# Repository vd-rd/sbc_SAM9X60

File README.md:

# Microchip SAM9X60 SBC

This board embeds a SIP (single core 600MHz ARM926 with 1Gb DDR2) with ACT8945a PMIC, IO headers and microSD/eMMC storage.

Board overview (draft):
[TBD]

## Board features
| Characteristic | Description |
| --- | --- |
| Dimensions | 60mm x 40mm |
| Processor | Microchip SAM9X60 @600MHz |
| Oscillators | 32.768kHz slow clock, 24MHz main clock |
| RAM | 128MB embedded DDR2 memory |
| Storage | microSD/eMMC |
| USB | 1 microUSB client |
| Ethernet | 2 10/100M RMII with pins on header |
| WiFi | 1 SDIO adapter with wifi/bt combo |
| Supply | Power path between USB/Vin/Battery, 5V max |

## Notes and observations
[TBD]

## Resources

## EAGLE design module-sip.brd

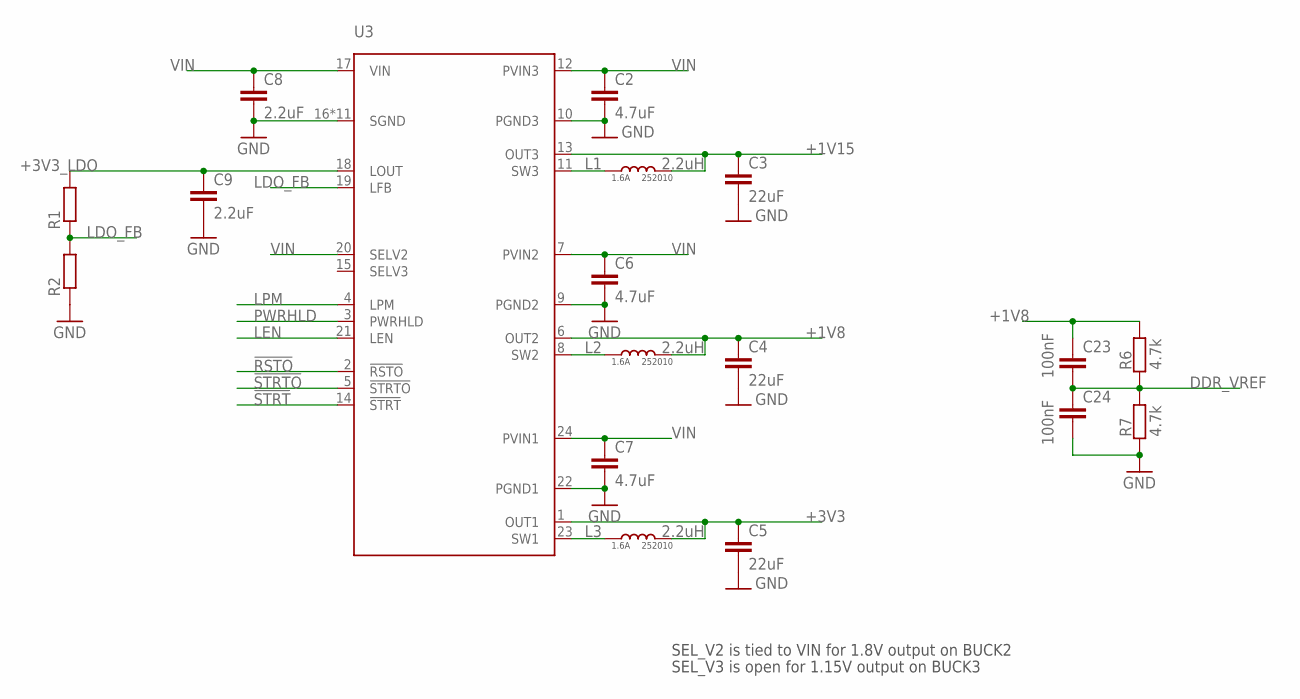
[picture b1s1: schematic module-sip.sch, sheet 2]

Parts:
C2, C6, C7: 4.7uF; C0603
C3, C4, C5: 22uF; C0805
C8, C9: 2.2uF; C0603
C23, C24: 100nF; C0402
L1, L2, L3: 2.2uH; INDUCTOR2520
R1, R2: R-EU_R0402; R0402
R6, R7: 4.7k; R0402
U3: MCP16501; QFN50P400X400X90-25T270N

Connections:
!RSTO: U3.2 (!RSTO)
!STRT: U3.14 (!STRT)
!STRTO: U3.5 (!STRTO)
+1V8: C4.1, C23.1, L2.P$2 (2), R6.2, U3.6 (OUT2); also elsewhere on the board
+1V15: C3.1, L1.P$2 (2), U3.13 (OUT3); also elsewhere on the board
+3V3: C5.1, L3.P$2 (2), U3.1 (OUT1); also elsewhere on the board
+3V3_LDO: C9.1, R1.2, U3.18 (LOUT)
DDR_VREF: C23.2, C24.1, R6.1, R7.2; also elsewhere on the board
GND: C2.2, C3.2, C4.2, C5.2, C6.2, C7.2, C8.2, C9.2, C24.2, R2.1, R7.1, U3.9 (PGND2), U3.10 (PGND3), U3.16 (SGND), U3.22 (PGND1), U3.25 (SGND), U3.P$1 (SGND), U3.P$2 (SGND), U3.P$3 (SGND), U3.P$4 (SGND), U3.P$5 (SGND), U3.P$6 (SGND), U3.P$7 (SGND), U3.P$8 (SGND), U3.P$9 (SGND); also elsewhere on the board
LDO_FB: R1.1, R2.2, U3.19 (LFB)
LEN: U3.21 (LEN)
LPM: U3.4 (LPM)
unnamed: L1.P$1 (1), U3.11 (SW3)
unnamed: L2.P$1 (1), U3.8 (SW2)
unnamed: L3.P$1 (1), U3.23 (SW1)
PWRHLD: U3.3 (PWRHLD)
VIN: C2.1, C6.1, C7.1, C8.1, U3.7 (PVIN2), U3.12 (PVIN3), U3.17 (VIN), U3.20 (SELV2), U3.24 (PVIN1)

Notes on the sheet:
SEL_V2 is tied to VIN for 1.8V output on BUCK2
SEL_V3 is open for 1.15V output on BUCK3

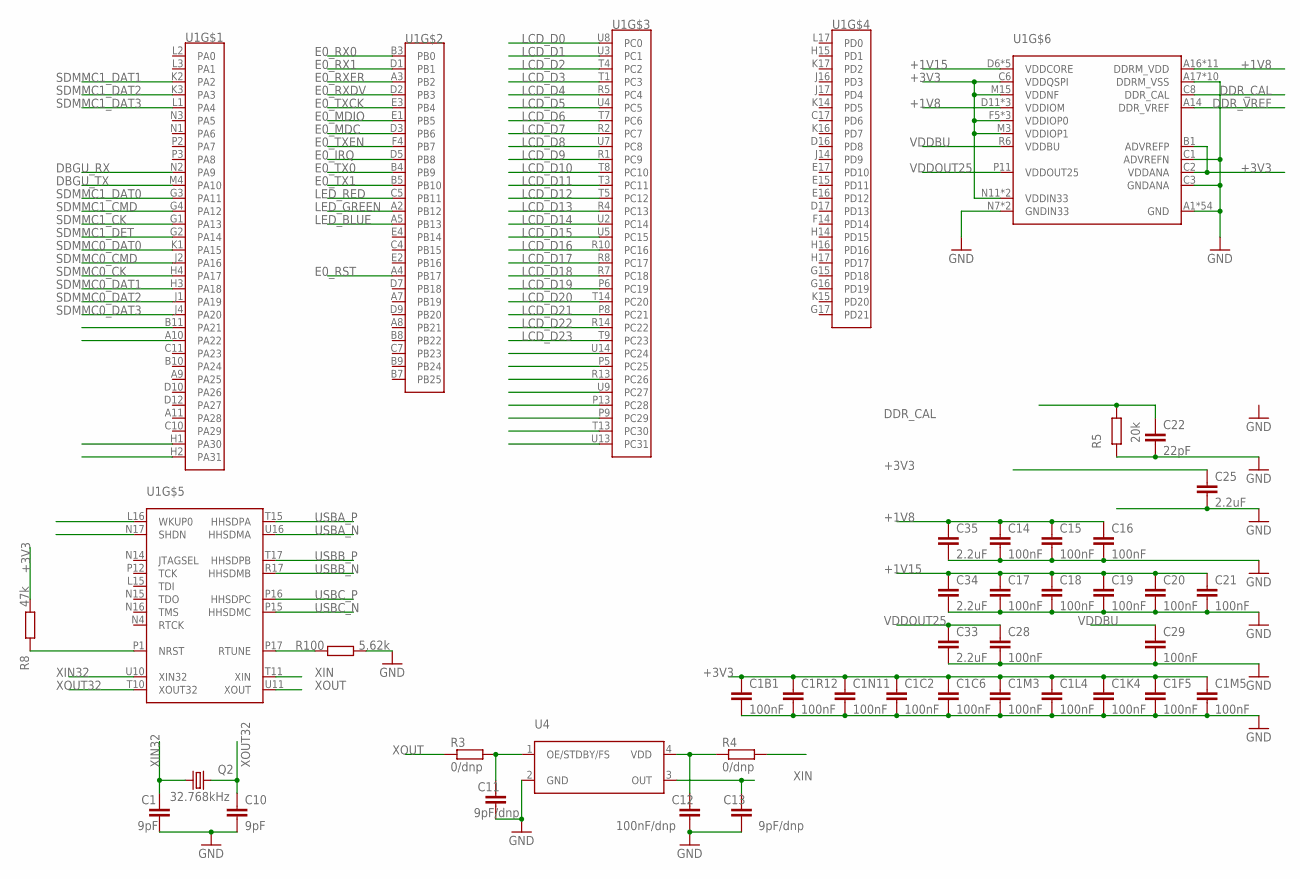
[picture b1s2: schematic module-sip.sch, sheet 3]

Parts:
C1, C10: 9pF; C0402
C1B1, C1C2, C1C6, C1F5, C1K4, C1L4, C1M3, C1M5, C1N11, C1R12, C14, C15, C16, C17, C18, C19, C20, C21, C28, C29: 100nF; C0201
C11, C13: 9pF/dnp; C0402
C12: 100nF/dnp; C0402
C22: 22pF; C0402
C25, C33, C34, C35: 2.2uF; C0402
Q2: 32.768kHz; 3215
R3, R4: 0/dnp; R0402
R5: 20k; R0402
R8: 47k; R0402
R100: 5.62k; R0402
U1: SAM9X60-D1G; BGA289C80P17X17_1400X1400X120N
U4: DSC1001CXX-024.0000; DFN320X250X90-4N

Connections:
+1V8: C14.1, C15.1, C16.1, C35.1, U1.A16 (DDRM_VDD), U1.B15 (DDRM_VDD), U1.B17 (DDRM_VDD), U1.C14 (DDRM_VDD), U1.C16 (DDRM_VDD), U1.D11 (VDDIOM), U1.D13 (DDRM_VDD), U1.D15 (DDRM_VDD), U1.E11 (DDRM_VDD), U1.E12 (DDRM_VDD), U1.E14 (VDDIOM), U1.F13 (DDRM_VDD), U1.G13 (DDRM_VDD), U1.G14 (VDDIOM); also elsewhere on the board
+1V15: C17.1, C18.1, C19.1, C20.1, C21.1, C34.1, U1.D6 (VDDCORE), U1.D8 (VDDCORE), U1.G5 (VDDCORE), U1.L6 (VDDCORE), U1.M7 (VDDCORE); also elsewhere on the board
+3V3: C1B1.1, C1C2.1, C1C6.1, C1F5.1, C1K4.1, C1L4.1, C1M3.1, C1M5.1, C1N11.1, C1R12.1, C25.1, R8.2, U1.B1 (ADVREFP), U1.C2 (VDDANA), U1.C6 (VDDQSPI), U1.F5 (VDDIOP0), U1.K4 (VDDIOP0), U1.L4 (VDDIOP0), U1.M3 (VDDIOP1), U1.M15 (VDDNF), U1.N11 (VDDIN33), U1.R12 (VDDIN33); also elsewhere on the board
DBGU_RX: U1.N2 (PA9); also elsewhere on the board
DBGU_TX: U1.M4 (PA10); also elsewhere on the board
DDR_CAL: C22.1, R5.1, U1.C8 (DDR_CAL)
DDR_VREF: U1.A14 (DDR_VREF); also elsewhere on the board
E0_IRQ: U1.D5 (PB8); also elsewhere on the board
E0_MDC: U1.D3 (PB6); also elsewhere on the board
E0_MDIO: U1.E1 (PB5); also elsewhere on the board
E0_RST: U1.A4 (PB17)
E0_RX0: U1.B3 (PB0); also elsewhere on the board
E0_RX1: U1.D1 (PB1); also elsewhere on the board
E0_RXDV: U1.D2 (PB3); also elsewhere on the board
E0_RXER: U1.A3 (PB2); also elsewhere on the board
E0_TX0: U1.B4 (PB9); also elsewhere on the board
E0_TX1: U1.B5 (PB10); also elsewhere on the board
E0_TXCK: U1.E3 (PB4); also elsewhere on the board
E0_TXEN: U1.F4 (PB7); also elsewhere on the board
GND: C1.2, C1B1.2, C1C2.2, C1C6.2, C1F5.2, C1K4.2, C1L4.2, C1M3.2, C1M5.2, C1N11.2, C1R12.2, C10.2, C11.2, C12.2, C13.2, C14.2, C15.2, C16.2, C17.2, C18.2, C19.2, C20.2, C21.2, C22.2, C25.2, C28.2, C29.2, C33.2, C34.2, C35.2, R5.2, R100.2, U1.A1 (GND), U1.A13 (GND), U1.A15 (GND), U1.A17 (DDRM_VSS), U1.B2 (GND), U1.B13 (GND), U1.B14 (GND), U1.B16 (DDRM_VSS), U1.C1 (ADVREFN), U1.C3 (GNDANA), U1.C9 (GND), U1.C12 (DDRM_VSS), U1.C13 (GND), U1.C15 (DDRM_VSS), U1.D4 (GND), U1.D14 (DDRM_VSS), U1.E5 (GND), U1.E6 (GND), U1.E7 (GND), U1.E13 (DDRM_VSS), U1.F3 (GND), U1.F6 (GND), U1.F7 (GND), U1.F11 (DDRM_VSS), U1.F12 (DDRM_VSS), U1.F15 (DDRM_VSS), U1.G6 (GND), U1.G12 (DDRM_VSS), U1.H8 (GND), U1.H9 (GND), U1.H10 (GND), U1.J3 (GND), U1.J8 (GND), U1.J9 (GND), U1.J10 (GND), U1.J15 (GND), U1.K8 (GND), U1.K9 (GND), U1.K10 (GND), U1.L5 (GND), U1.L12 (GND), U1.L13 (GND), U1.L14 (GND), U1.M5 (GND), U1.M6 (GND), U1.M11 (GND), U1.M12 (GND), U1.M13 (GND), U1.M14 (GND), U1.N5 (GND), U1.N6 (GND), U1.N7 (GNDIN33), U1.N12 (GND), U1.N13 (GND), U1.P4 (GND), U1.P7 (GNDIN33), U1.P10 (GND), U1.P14 (GND), U1.R3 (GND), U1.R9 (GND), U1.R11 (GND), U1.R15 (GND), U1.R16 (GND), U1.T2 (GND), U1.T16 (GND), U1.U1 (GND), U1.U15 (GND), U1.U17 (GND), U4.2 (GND); also elsewhere on the board
LCD_D0: U1.U8 (PC0)
LCD_D1: U1.U3 (PC1)
LCD_D2: U1.T4 (PC2)
LCD_D3: U1.T1 (PC3)
LCD_D4: U1.R5 (PC4)
LCD_D5: U1.U4 (PC5)
LCD_D6: U1.T7 (PC6)
LCD_D7: U1.R2 (PC7)
LCD_D8: U1.U7 (PC8)
LCD_D9: U1.R1 (PC9)
LCD_D10: U1.T8 (PC10)
LCD_D11: U1.T3 (PC11)
LCD_D12: U1.T5 (PC12)
LCD_D13: U1.R4 (PC13)
LCD_D14: U1.U2 (PC14)
LCD_D15: U1.U5 (PC15)
LCD_D16: U1.R10 (PC16)
LCD_D17: U1.R8 (PC17)
LCD_D18: U1.R7 (PC18)
LCD_D19: U1.P6 (PC19)
LCD_D20: U1.T14 (PC20)
LCD_D21: U1.P8 (PC21)
LCD_D22: U1.R14 (PC22)
LCD_D23: U1.T9 (PC23)
LED_BLUE: U1.A5 (PB13); also elsewhere on the board
LED_GREEN: U1.A2 (PB12); also elsewhere on the board
LED_RED: U1.C5 (PB11); also elsewhere on the board
unnamed: C12.1, R4.1, U4.4 (VDD)
unnamed: C11.1, R3.2, U4.1 (OE/STDBY/FS)
unnamed: R8.1, U1.P1 (NRST)
unnamed: R100.1, U1.P17 (RTUNE)
SDMMC0_CK: U1.H4 (PA17)
SDMMC0_CMD: U1.J2 (PA16); also elsewhere on the board
SDMMC0_DAT0: U1.K1 (PA15); also elsewhere on the board
SDMMC0_DAT1: U1.H3 (PA18); also elsewhere on the board
SDMMC0_DAT2: U1.J1 (PA19); also elsewhere on the board
SDMMC0_DAT3: U1.J4 (PA20); also elsewhere on the board
SDMMC1_CK: U1.G1 (PA13); also elsewhere on the board
SDMMC1_CMD: U1.G4 (PA12); also elsewhere on the board
SDMMC1_DAT0: U1.G3 (PA11); also elsewhere on the board
SDMMC1_DAT1: U1.K2 (PA2); also elsewhere on the board
SDMMC1_DAT2: U1.K3 (PA3); also elsewhere on the board
SDMMC1_DAT3: U1.L1 (PA4); also elsewhere on the board
SDMMC1_DET: U1.G2 (PA14); also elsewhere on the board
USBA_N: U1.U16 (HHSDMA); also elsewhere on the board
USBA_P: U1.T15 (HHSDPA); also elsewhere on the board
USBB_N: U1.R17 (HHSDMB); also elsewhere on the board
USBB_P: U1.T17 (HHSDPB); also elsewhere on the board
USBC_N: U1.P15 (HHSDMC); also elsewhere on the board
USBC_P: U1.P16 (HHSDPC); also elsewhere on the board
VDDBU: C29.1, U1.R6 (VDDBU)
VDDOUT25: C28.1, C33.1, U1.P11 (VDDOUT25)
XIN: C13.1, U1.T11 (XIN), U4.3 (OUT)
XIN32: C1.1, Q2.1, U1.U10 (XIN32)
XOUT: R3.1, U1.U11 (XOUT)
XOUT32: C10.1, Q2.2, U1.T10 (XOUT32)

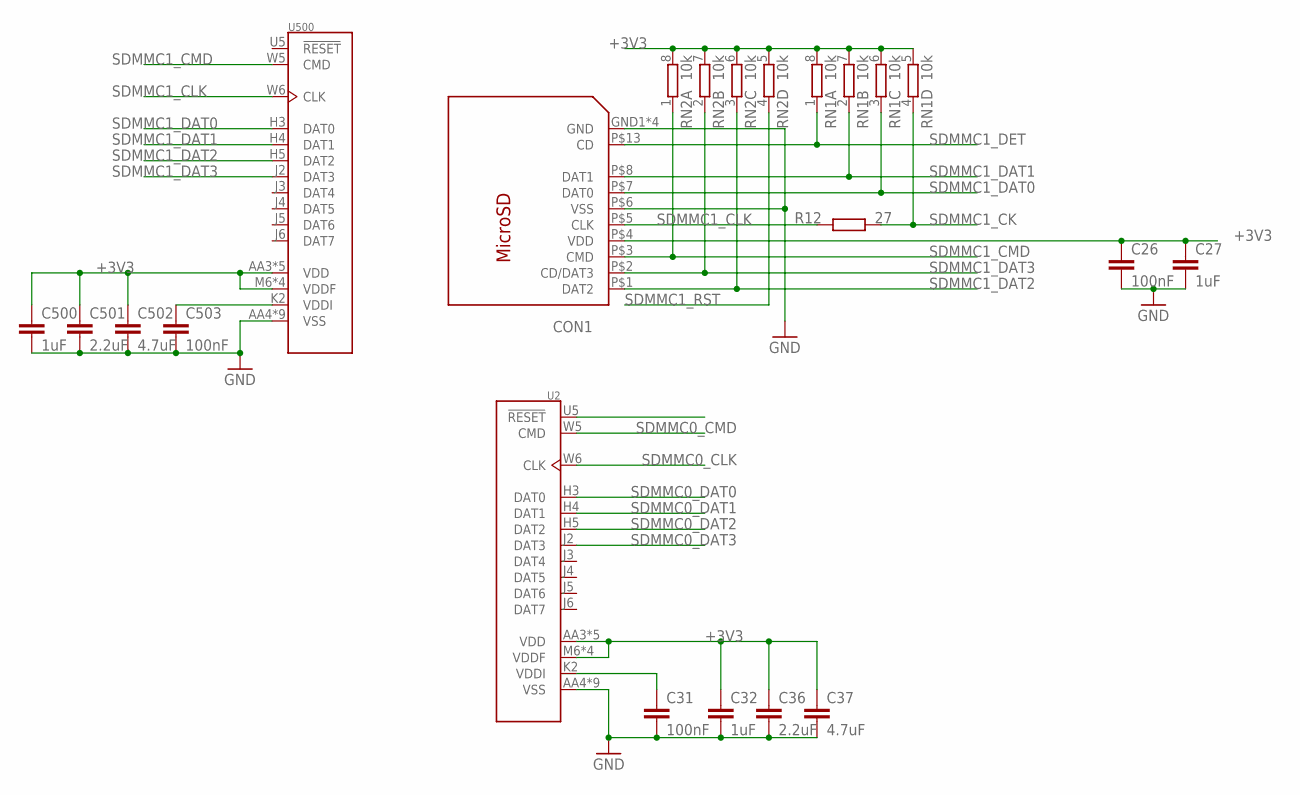
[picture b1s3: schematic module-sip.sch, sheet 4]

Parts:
C26, C31, C503: 100nF; C0402
C27, C32, C500: 1uF; C0402
C36, C501: 2.2uF; C0402
C37, C502: 4.7uF; C0402
CON1: 112J-TXAR; 112J
R12: 27; R0402
RN1, RN2: 10k; 4X0402ARV341
U2, U500: KLMXGXGE4A-A001; BGA169C50P14X28_1600X1200X120N

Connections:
+3V3: C26.1, C27.1, C32.1, C36.1, C37.1, C500.1, C501.1, C502.1, CON1.P$4 (VDD), RN1.5 (2), RN1.6 (2), RN1.7 (2), RN1.8 (2), RN2.5 (2), RN2.6 (2), RN2.7 (2), RN2.8 (2), U2.AA3 (VDD), U2.AA5 (VDD), U2.K6 (VDD), U2.M6 (VDDF), U2.N5 (VDDF), U2.T10 (VDDF), U2.U9 (VDDF), U2.W4 (VDD), U2.Y4 (VDD), U500.AA3 (VDD), U500.AA5 (VDD), U500.K6 (VDD), U500.M6 (VDDF), U500.N5 (VDDF), U500.T10 (VDDF), U500.U9 (VDDF), U500.W4 (VDD), U500.Y4 (VDD); also elsewhere on the board
GND: C26.2, C27.2, C31.2, C32.2, C36.2, C37.2, C500.2, C501.2, C502.2, C503.2, CON1.GND1 (GND), CON1.GND2 (GND), CON1.GND3 (GND), CON1.GND4 (GND), CON1.P$6 (VSS), U2.AA4 (VSS), U2.AA6 (VSS), U2.K4 (VSS), U2.M7 (VSS), U2.P5 (VSS), U2.R10 (VSS), U2.U8 (VSS), U2.Y2 (VSS), U2.Y5 (VSS), U500.AA4 (VSS), U500.AA6 (VSS), U500.K4 (VSS), U500.M7 (VSS), U500.P5 (VSS), U500.R10 (VSS), U500.U8 (VSS), U500.Y2 (VSS), U500.Y5 (VSS); also elsewhere on the board
unnamed: C503.1, U500.K2 (VDDI)
unnamed: C31.1, U2.K2 (VDDI)
SDMMC0_CLK: U2.W6 (CLK)
SDMMC0_CMD: U2.W5 (CMD); also elsewhere on the board
SDMMC0_DAT0: U2.H3 (DAT0); also elsewhere on the board
SDMMC0_DAT1: U2.H4 (DAT1); also elsewhere on the board
SDMMC0_DAT2: U2.H5 (DAT2); also elsewhere on the board
SDMMC0_DAT3: U2.J2 (DAT3); also elsewhere on the board
SDMMC1_CK: R12.2, RN1.4 (1); also elsewhere on the board
SDMMC1_CLK: CON1.P$5 (CLK), R12.1, U500.W6 (CLK)
SDMMC1_CMD: CON1.P$3 (CMD), RN2.1, U500.W5 (CMD); also elsewhere on the board
SDMMC1_DAT0: CON1.P$7 (DAT0), RN1.3 (1), U500.H3 (DAT0); also elsewhere on the board
SDMMC1_DAT1: CON1.P$8 (DAT1), RN1.2 (1), U500.H4 (DAT1); also elsewhere on the board
SDMMC1_DAT2: CON1.P$1 (DAT2), RN2.3 (1), U500.H5 (DAT2); also elsewhere on the board
SDMMC1_DAT3: CON1.P$2 (CD/DAT3), RN2.2 (1), U500.J2 (DAT3); also elsewhere on the board
SDMMC1_DET: CON1.P$13 (CD), RN1.1; also elsewhere on the board
SDMMC1_RST: RN2.4 (1)

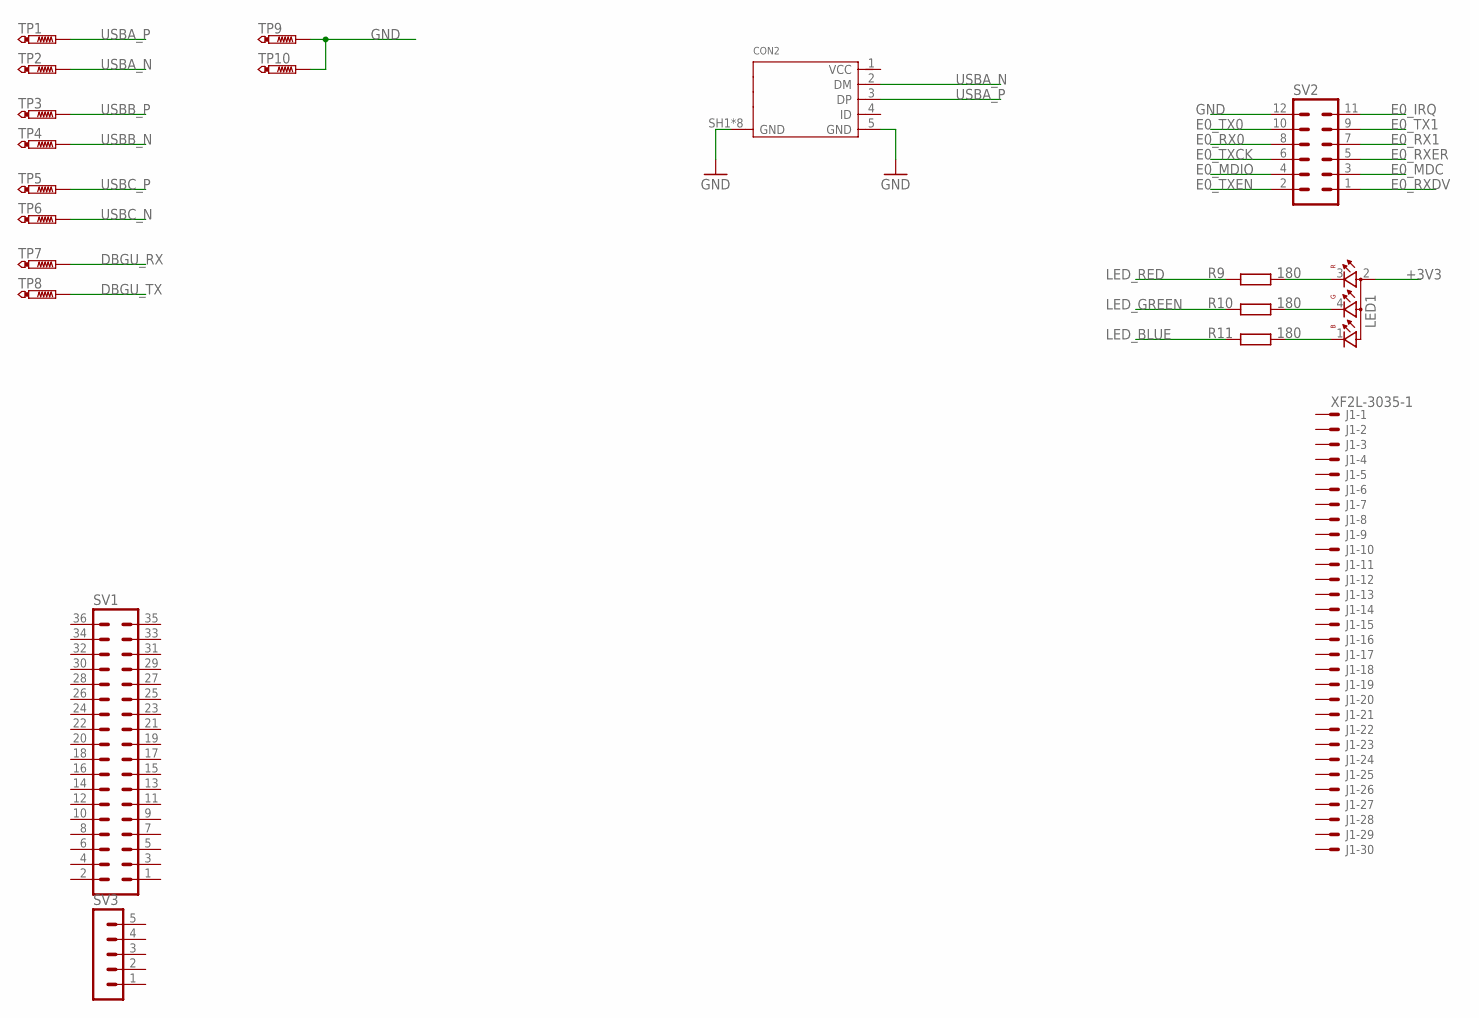
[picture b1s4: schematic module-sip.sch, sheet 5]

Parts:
CON2: 10118194-0001LF; 10118194
J1: XF2L-3035-1
LED1: OSTB1204C1E; 321015RGB
R9, R10, R11: 180; R0402
SV1: MA18-2
SV2: MA06-2
SV3: MA05-1
TP1, TP2, TP3, TP4, TP5, TP6, TP7, TP8, TP9, TP10: PTR1B1,27; B1,27

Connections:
+3V3: LED1.2 (CC); also elsewhere on the board
DBGU_RX: TP7.TP; also elsewhere on the board
DBGU_TX: TP8.TP; also elsewhere on the board
E0_IRQ: SV2.11; also elsewhere on the board
E0_MDC: SV2.3; also elsewhere on the board
E0_MDIO: SV2.4; also elsewhere on the board
E0_RX0: SV2.8; also elsewhere on the board
E0_RX1: SV2.7; also elsewhere on the board
E0_RXDV: SV2.1; also elsewhere on the board
E0_RXER: SV2.5; also elsewhere on the board
E0_TX0: SV2.10; also elsewhere on the board
E0_TX1: SV2.9; also elsewhere on the board
E0_TXCK: SV2.6; also elsewhere on the board
E0_TXEN: SV2.2; also elsewhere on the board
GND: CON2.5 (GND), CON2.SH1 (GND), CON2.SH2 (GND), CON2.SH3 (GND), CON2.SH4 (GND), CON2.SH5 (GND), CON2.SH6 (GND), CON2.SH7 (GND), CON2.SH8 (GND), SV2.12, TP9.TP, TP10.TP; also elsewhere on the board
LED_BLUE: R11.1; also elsewhere on the board
LED_GREEN: R10.1; also elsewhere on the board
LED_RED: R9.1; also elsewhere on the board
unnamed: LED1.3 (AR), R9.2
unnamed: LED1.4 (AG), R10.2
unnamed: LED1.1 (AB), R11.2
USBA_N: CON2.2 (DM), TP2.TP; also elsewhere on the board
USBA_P: CON2.3 (DP), TP1.TP; also elsewhere on the board
USBB_N: TP4.TP; also elsewhere on the board
USBB_P: TP3.TP; also elsewhere on the board
USBC_N: TP6.TP; also elsewhere on the board
USBC_P: TP5.TP; also elsewhere on the board

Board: 2 copper layers, 91 parts (32 on the bottom side), 62 nets, no tracks yet.

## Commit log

2021-02-27 project: add sip module
2021-02-27 project: add discrete module
2021-03-02 project: add sip version footprint
2021-03-02 discrete: add decoupling caps
2021-03-02 sip: add nand
2021-03-02 sip: add pmic
2021-03-02 branch sip module
2021-03-02 add crystal for mcu
2021-03-02 prelim defining of power rails
2021-03-03 define power rails and caps
2021-03-03 pmic: define power rails
2021-03-03 add initial pin definiton
2021-03-03 add io connectors
2021-03-03 board refactoring
2021-03-03 add rmii connector
2021-03-03 add user leds
2021-03-03 add stprage options
2021-03-03 add usb lines
2021-03-04 add assembly variants
2021-05-25 add kicad filters in gitignore
2021-05-25 adding kicad project
2021-05-25 defined board shape & placement
2021-05-26 added power rails
2021-05-26 added io connectors
2021-05-26 added rmii and usb
2021-05-26 add sdcard
2021-05-26 define gpio assignments
2021-05-28 define flexcom assignment
2021-05-29 add new components
2021-06-14 added wifi sdio
2021-06-14 updated sdio connexions
2021-06-17 wifi module sch capture
2021-06-17 initial power stage routing
2021-06-24 layout improvements
2021-08-20 updated module
2021-09-02 changed board mechanical layout
2021-10-06 swapped pmic for act9845A
2021-10-06 udpdated connectors and floorplan
2021-10-10 improve component placement
2021-10-19 more routing
2021-11-13 defined connections
2021-11-14 defined more cpu signals
2021-12-12 fixed button position
2022-01-04 reposition components
2022-01-04 add nor and led driver
2022-01-04 add board render
2022-01-11 small changes in layout
2022-01-13 more routing for lcd signals
2022-01-16 add layer identification labels
2022-01-29 remove lcd fpc connector
2022-01-30 add new lcd connector
2022-02-22 define pmic zone
2024-03-19 board definition
2024-03-19 cleanup
2024-03-19 cleanup project space
2024-03-21 add and align functionality
2024-08-05 defined sip specs
